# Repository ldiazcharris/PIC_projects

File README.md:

# PIC_projects
Proyectos de clase sobre conceptos básicos de programación con microcontroladores PIC.

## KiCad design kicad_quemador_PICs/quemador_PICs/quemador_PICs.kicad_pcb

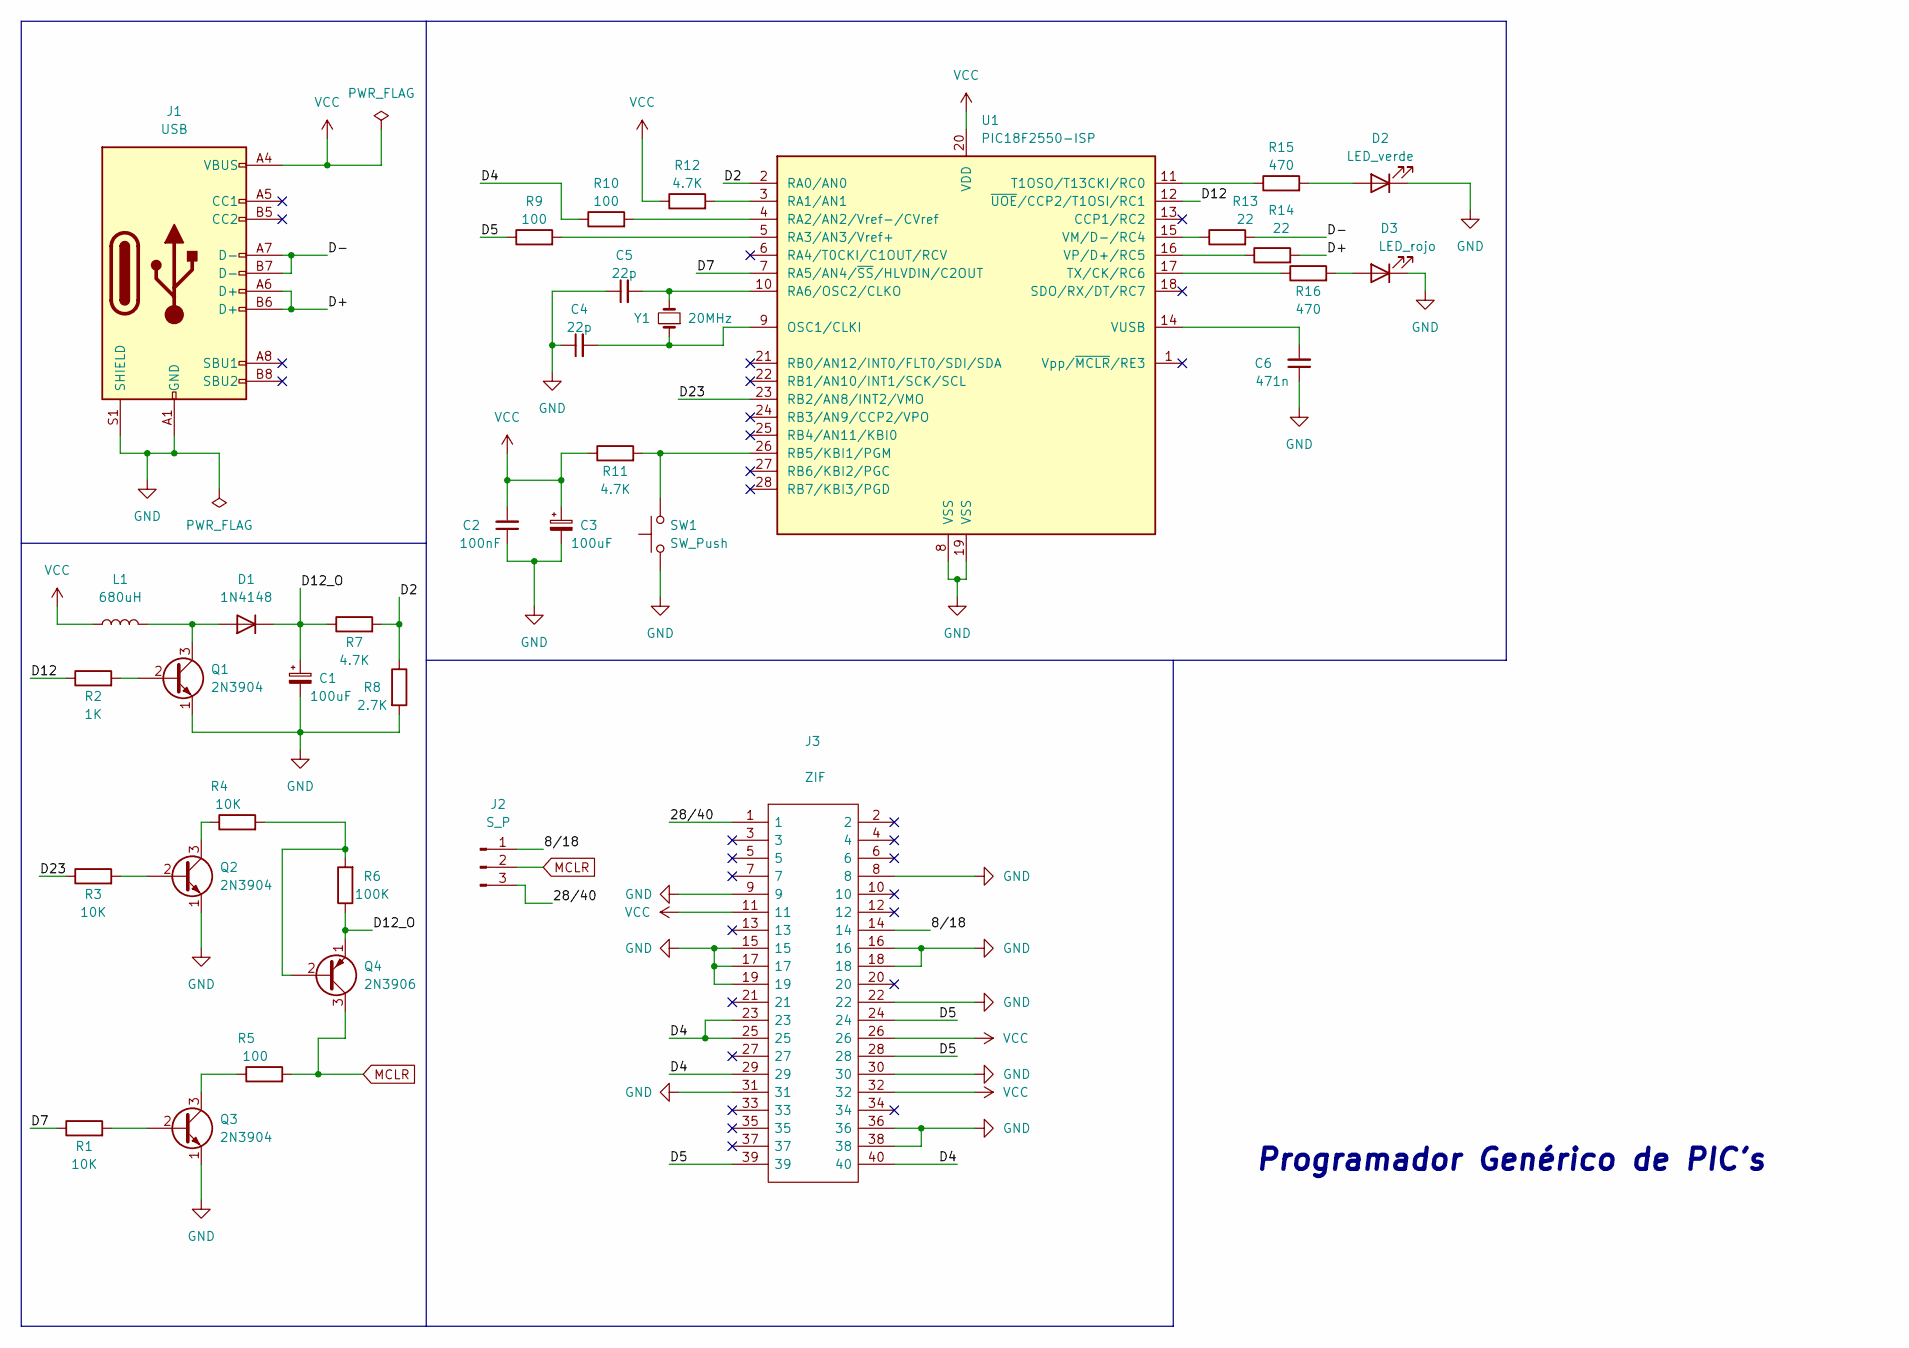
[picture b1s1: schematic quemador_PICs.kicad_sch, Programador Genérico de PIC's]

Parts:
C1, C3: 100uF; CP_Radial_D8.0mm_P5.00mm
C2: 100nF; C_Disc_D3.0mm_W1.6mm_P2.50mm
C4, C5: 22p; C_Disc_D3.0mm_W1.6mm_P2.50mm
C6: 471n; C_Disc_D3.0mm_W1.6mm_P2.50mm
D1: 1N4148; D_DO-35_SOD27_P7.62mm_Horizontal
D2: LED_verde; LED_D1.8mm_W3.3mm_H2.4mm
D3: LED_rojo; LED_D1.8mm_W3.3mm_H2.4mm
J1: USB
J2: S_P; PinHeader_1x03_P2.54mm_Vertical
J3: ZIF; 2401288000602J; Manufacturer_Part_Number 240-1288-00-0602J; Mouser Part Number 517-240-1288-00
L1: 680uH; L_Axial_L5.3mm_D2.2mm_P10.16mm_Horizontal_Vishay_IM-1
Q1, Q2, Q3: 2N3904; TO-92_Inline
Q4: 2N3906; TO-92_Inline
R1, R3, R4: 10K; R_Axial_DIN0204_L3.6mm_D1.6mm_P5.08mm_Horizontal
R2: 1K; R_Axial_DIN0204_L3.6mm_D1.6mm_P5.08mm_Horizontal
R5, R9, R10: 100; R_Axial_DIN0204_L3.6mm_D1.6mm_P5.08mm_Horizontal
R6: 100K; R_Axial_DIN0204_L3.6mm_D1.6mm_P5.08mm_Horizontal
R7, R11, R12: 4.7K; R_Axial_DIN0204_L3.6mm_D1.6mm_P5.08mm_Horizontal
R8: 2.7K; R_Axial_DIN0204_L3.6mm_D1.6mm_P5.08mm_Horizontal
R13, R14: 22; R_Axial_DIN0204_L3.6mm_D1.6mm_P5.08mm_Horizontal
R15, R16: 470; R_Axial_DIN0204_L3.6mm_D1.6mm_P5.08mm_Horizontal
SW1: SW_Push; SW_PUSH_6mm_H7.3mm
U1: PIC18F2550-ISP; DIP-28_W7.62mm
Y1: 20MHz; Crystal_HC18-U_Vertical

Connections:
/8/18: J2.1, J3.14
/28/40: J2.3, J3.1
/D2: R7.2, R8.1, U1.2 (RA0/AN0)
/D4: J3.23, J3.25, J3.29, J3.40, R10.1
/D5: J3.24, J3.28, J3.39, R9.1
/D7: R1.1, U1.7 (RA5/AN4/~SS/HLVDIN/C2OUT)
/D12: R2.1, U1.12 (~UOE/CCP2/T1OSI/RC1)
/D12_O: C1.1, D1.1 (K), Q4.1 (E), R6.1, R7.1
/D23: R3.1, U1.23 (RB2/AN8/INT2/VMO)
/D+: J1.A6 (D+), J1.B6 (D+), R14.2
/D-: J1.A7 (D-), J1.B7 (D-), R13.2
GND: C1.2, C2.1, C3.2, C4.1, C5.1, C6.1, D2.1 (K), D3.1 (K), J1.A1 (GND), J1.A12 (GND), J1.B1 (GND), J1.B12 (GND), J1.S1 (SHIELD), J3.8, J3.9, J3.15, J3.16, J3.17, J3.18, J3.19, J3.22, J3.30, J3.31, J3.36, J3.38, Q1.1 (E), Q2.1 (E), Q3.1 (E), R8.2, SW1.1, U1.8 (VSS), U1.19 (VSS)
MCLR: J2.2, Q4.3 (C), R5.2
unnamed: C4.2, U1.9 (OSC1/CLKI), Y1.1
unnamed: C5.2, U1.10 (RA6/OSC2/CLKO), Y1.2
unnamed: C6.2, U1.14 (VUSB)
unnamed: D1.2 (A), L1.2, Q1.3 (C)
unnamed: D2.2 (A), R15.2
unnamed: D3.2 (A), R16.2
unnamed: Q1.2 (B), R2.2
unnamed: Q2.2 (B), R3.2
unnamed: Q2.3 (C), R4.1
unnamed: Q3.2 (B), R1.2
unnamed: Q3.3 (C), R5.1
unnamed: Q4.2 (B), R4.2, R6.2
unnamed: R9.2, U1.5 (RA3/AN3/Vref+)
unnamed: R10.2, U1.4 (RA2/AN2/Vref-/CVref)
unnamed: R11.2, SW1.2, U1.26 (RB5/KBI1/PGM)
unnamed: R12.2, U1.3 (RA1/AN1)
unnamed: R13.1, U1.15 (VM/D-/RC4)
unnamed: R14.1, U1.16 (VP/D+/RC5)
unnamed: R15.1, U1.11 (T1OSO/T13CKI/RC0)
unnamed: R16.1, U1.17 (TX/CK/RC6)
VCC: C2.2, C3.1, J1.A4 (VBUS), J1.A9 (VBUS), J1.B4 (VBUS), J1.B9 (VBUS), J3.11, J3.26, J3.32, L1.1, R11.1, R12.1, U1.20 (VDD)

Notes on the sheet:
Programador Genérico de PIC's

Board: 2 copper layers, 36 parts (0 on the bottom side), 34 nets, no tracks yet.

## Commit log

2022-11-22 commit inicial
2022-11-23 adding a generic pic programmer
2022-11-23 Purge
